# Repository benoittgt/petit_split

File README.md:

# Petit Split - Benoit version

This is inspired by Foostan book and petit split project.

## Status

Few errors. See report_drc.rpt

## Footprint libraries used

* https://github.com/keebio/Keebio-Parts.pretty
* https://github.com/foostan/kbd
* Shiba included in this repo

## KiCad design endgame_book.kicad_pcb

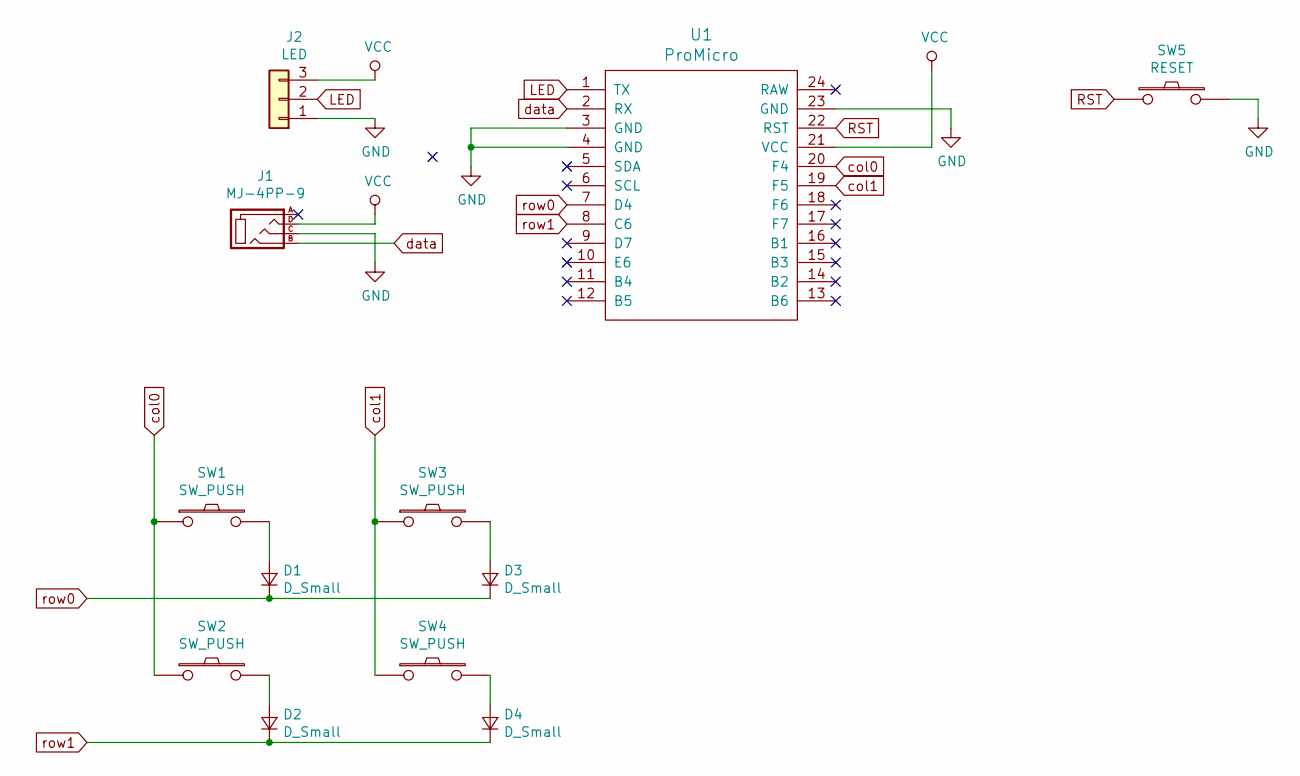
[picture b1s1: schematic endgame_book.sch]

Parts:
D1, D2, D3, D4: D_Small; D3_SMD
J1: MJ-4PP-9
J2: LED; StripLED_rev
SW1, SW2, SW3, SW4: SW_PUSH; CherryMX_Choc_1u
SW5: RESET; ResetSW
U1: ProMicro; ProMicro_v2

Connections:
GND: J1.C, J2.1, SW5.2, U1.3 (GND), U1.4 (GND), U1.23 (GND)
LED: J2.2, U1.1 (TX)
unnamed: D1.2 (A), SW1.2
unnamed: D2.2 (A), SW2.2
unnamed: D3.2 (A), SW3.2
unnamed: D4.2 (A), SW4.2
RST: SW5.1, U1.22 (RST)
VCC: J1.D, J2.3, U1.21 (VCC)
col0: SW1.1, SW2.1, U1.20 (F4)
col1: SW3.1, SW4.1, U1.19 (F5)
data: J1.B, U1.2 (RX)
row0: D1.1 (K), D3.1 (K), U1.7 (D4)
row1: D2.1 (K), D4.1 (K), U1.8 (C6)

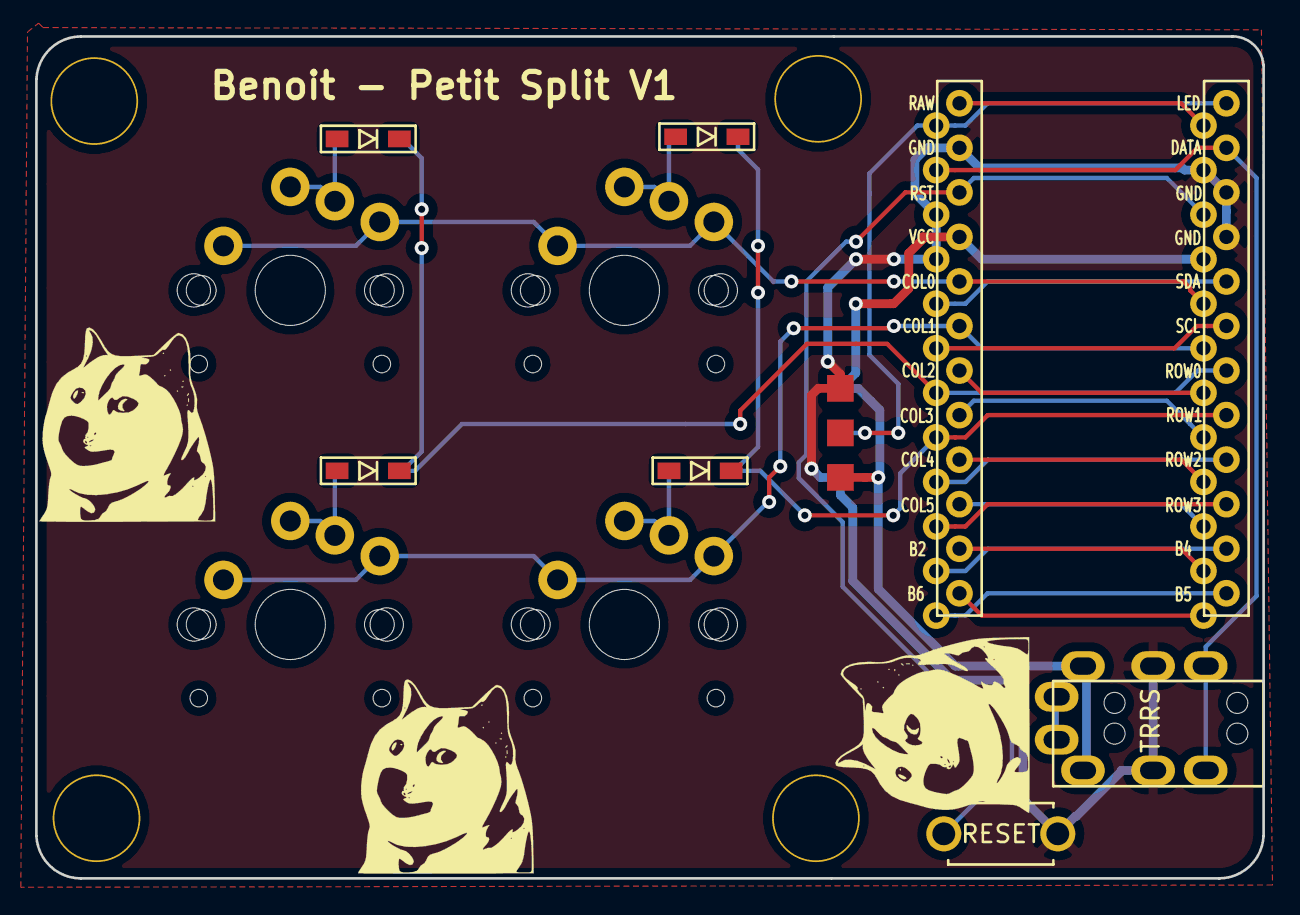
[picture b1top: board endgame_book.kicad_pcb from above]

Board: 2 copper layers, 70.0 x 48.0 mm, 16 parts (0 on the bottom side), 13 nets.

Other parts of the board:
Ref**: Val**; HOLE
Ref**#2, Ref**#3, Ref**#4: Val**; HOLE

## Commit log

2019-05-27 First version with DRC errors
